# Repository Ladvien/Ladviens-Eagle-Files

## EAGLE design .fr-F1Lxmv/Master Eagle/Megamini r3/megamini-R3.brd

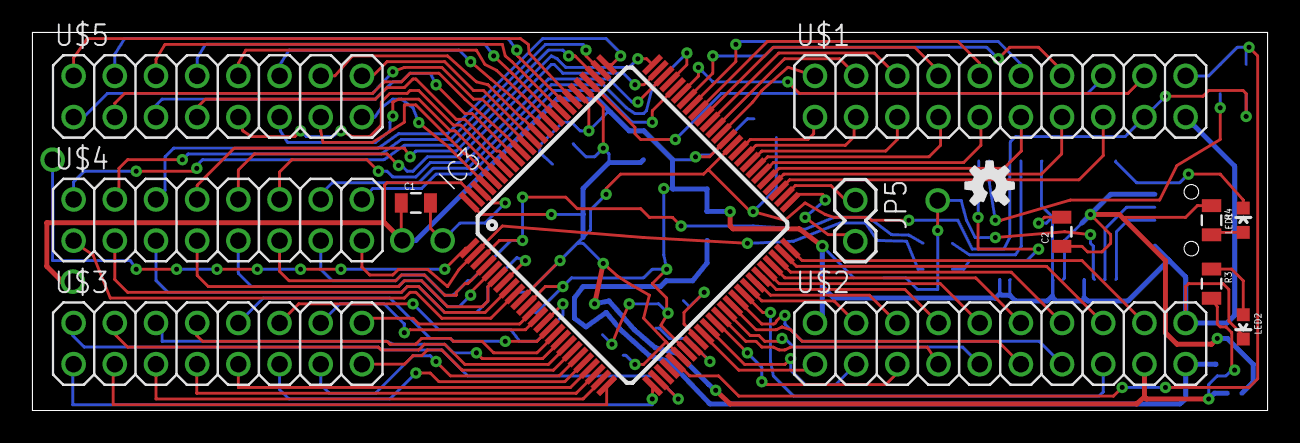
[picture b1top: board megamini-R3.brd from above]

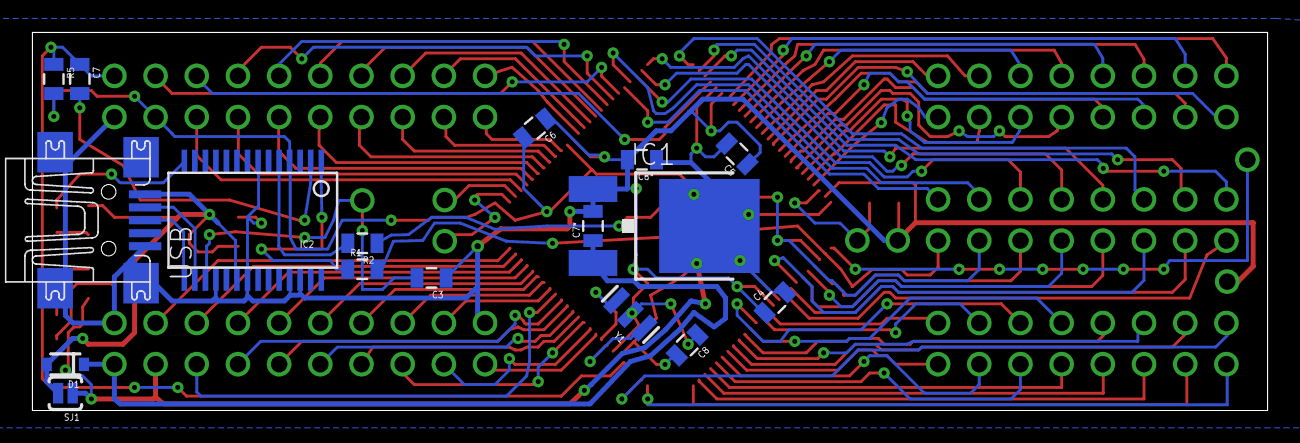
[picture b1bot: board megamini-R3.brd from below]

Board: 2 copper layers, 76.2 x 23.3 mm, 37 parts (17 on the bottom side), 101 nets.

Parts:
C1, C2, C3, C4, C5, C6, C7, C8: 100nF; 0805
C7*, C8*: 10uF; 0805
D1: SOD-323
IC1: NCP1117-5.0; DPACK
IC2: FT232RLSSOP; SSOP28DB
IC3: ATMEGA2560-16AU; TQFP100
JP1, JP2, JP3, JP4, JP6: M01SMDNS; 1X01NS
JP5: 1X02
LED1, LED2: LED-0603
R1, R2, R3, R4: 0805
R5: 10k; 0805
SJ1: SOLDERJUMPERNO; SJ_2S-NO
U$1, U$2: M10X2; 2X10
U$3, U$4, U$5: M08X2; 2X8_SMALL
U$6: OSHW-LOGOS; OSHW-LOGO-S
U$7: CREATIVE_COMMONS
USB: UX60-MB-5ST
Y1: RESONATORSMD; RESONATOR-SMD

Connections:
G0: IC3.51, JP5.2
G1: IC3.52, JP5.1
G2: IC3.70, U$1.18
GND: C1.1, C2.2, C3.1, C4.1, C5.1, C6.1, C7*.2, C8.1, C8*.2, IC1.1, IC2.7, IC2.18, IC2.21, IC2.25, IC2.26, IC3.11, IC3.32, IC3.62, IC3.81, IC3.99, JP2.1, JP3.1, LED2.C, U$1.19, U$2.2, U$2.20, USB.5, Y1.2
unnamed: IC2.16, USB.2
unnamed: IC3.1, JP1.1
unnamed: IC2.15, USB.3
unnamed: C7.2, IC2.2
unnamed: IC2.1, R1.1
unnamed: IC2.5, R2.2
unnamed: C3.2, IC2.17, JP4.1
unnamed: IC3.33, Y1.1
unnamed: IC3.34, Y1.3
unnamed: LED2.A, R3.1
unnamed: LED1.A, R4.2
unnamed: IC2.14, LED1.C
unnamed: C1.2, IC3.98, JP6.1
PA0: IC3.78, U$4.2
PA1: IC3.77, U$4.4
PA2: IC3.76, U$4.6
PA3: IC3.75, U$4.8
PA4: IC3.74, U$4.10
PA5: IC3.73, U$4.12
PA6: IC3.72, U$4.14
PA7: IC3.71, U$4.16
PB0: IC3.19, U$3.15
PB1: IC3.20, U$3.13
PB2: IC3.21, U$3.11
PB3: IC3.22, U$3.9
PB4: IC3.23, U$3.7
PB5: IC3.24, U$3.5
PB6: IC3.25, U$3.3
PB7: IC3.26, U$3.1
PC0: IC3.53, U$1.15
PC1: IC3.54, U$1.13
PC2: IC3.55, U$1.11
PC3: IC3.56, U$1.9
PC4: IC3.57, U$1.7
PC5: IC3.58, U$1.5
PC6: IC3.59, U$1.3
PC7: IC3.60, U$1.1
PD0: IC3.43, U$2.4
PD1: IC3.44, U$2.6
PD2: IC3.45, U$2.8
PD3: IC3.46, U$2.10
PD4: IC3.47, U$2.12
PD5: IC3.48, U$2.14
PD6: IC3.49, U$2.16
PD7: IC3.50, U$2.18
PE0: IC3.2, R1.2, U$4.15
PE1: IC3.3, R2.1, U$4.13
PE2: IC3.4, U$4.11
PE3: IC3.5, U$4.9
PE4: IC3.6, U$4.7
PE5: IC3.7, U$4.5
PE6: IC3.8, U$4.3
PE7: IC3.9, U$4.1
PF0: IC3.97, U$5.15
PF1: IC3.96, U$5.13
PF2: IC3.95, U$5.11
PF3: IC3.94, U$5.9
PF4: IC3.93, U$5.7
PF5: IC3.92, U$5.5
PF6: IC3.91, U$5.3
PF7: IC3.90, U$5.1
PH0: IC3.12, U$3.16
PH1: IC3.13, U$3.14
PH2: IC3.14, U$3.12
PH3: IC3.15, U$3.10
PH4: IC3.16, U$3.8
PH5: IC3.17, U$3.6
PH6: IC3.18, U$3.4
PH7: IC3.27, U$3.2
PJ0: IC3.63, U$1.2
PJ1: IC3.64, U$1.4
PJ2: IC3.65, U$1.6
PJ3: IC3.66, U$1.8
PJ4: IC3.67, U$1.10
PJ5: IC3.68, U$1.12
PJ6: IC3.69, U$1.14
PJ7: IC3.79, U$1.16
PK0: IC3.89, U$5.16
PK1: IC3.88, U$5.14
PK2: IC3.87, U$5.12
PK3: IC3.86, U$5.10
PK4: IC3.85, U$5.8
PK5: IC3.84, U$5.6
PK6: IC3.83, U$5.4
PK7: IC3.82, U$5.2
PL0: IC3.35, U$2.1
PL1: IC3.36, U$2.3
PL2: IC3.37, U$2.5
PL3: IC3.38, U$2.7
PL4: IC3.39, U$2.9
PL5: IC3.40, U$2.11
PL6: IC3.41, U$2.13
PL7: IC3.42, U$2.15
RESET: C7.1, IC3.30, R5.1, U$1.20
USB5V: C2.1, D1.2, IC2.20, R4.1, SJ1.2, USB.1
VCC: C4.2, C5.2, C6.2, C8.2, C8*.1, IC1.4, IC2.4, IC3.10, IC3.31, IC3.61, IC3.80, IC3.100, R3.2, R5.2, SJ1.1, U$1.17, U$2.17
VIN: C7*.1, D1.1, IC1.3, U$2.19

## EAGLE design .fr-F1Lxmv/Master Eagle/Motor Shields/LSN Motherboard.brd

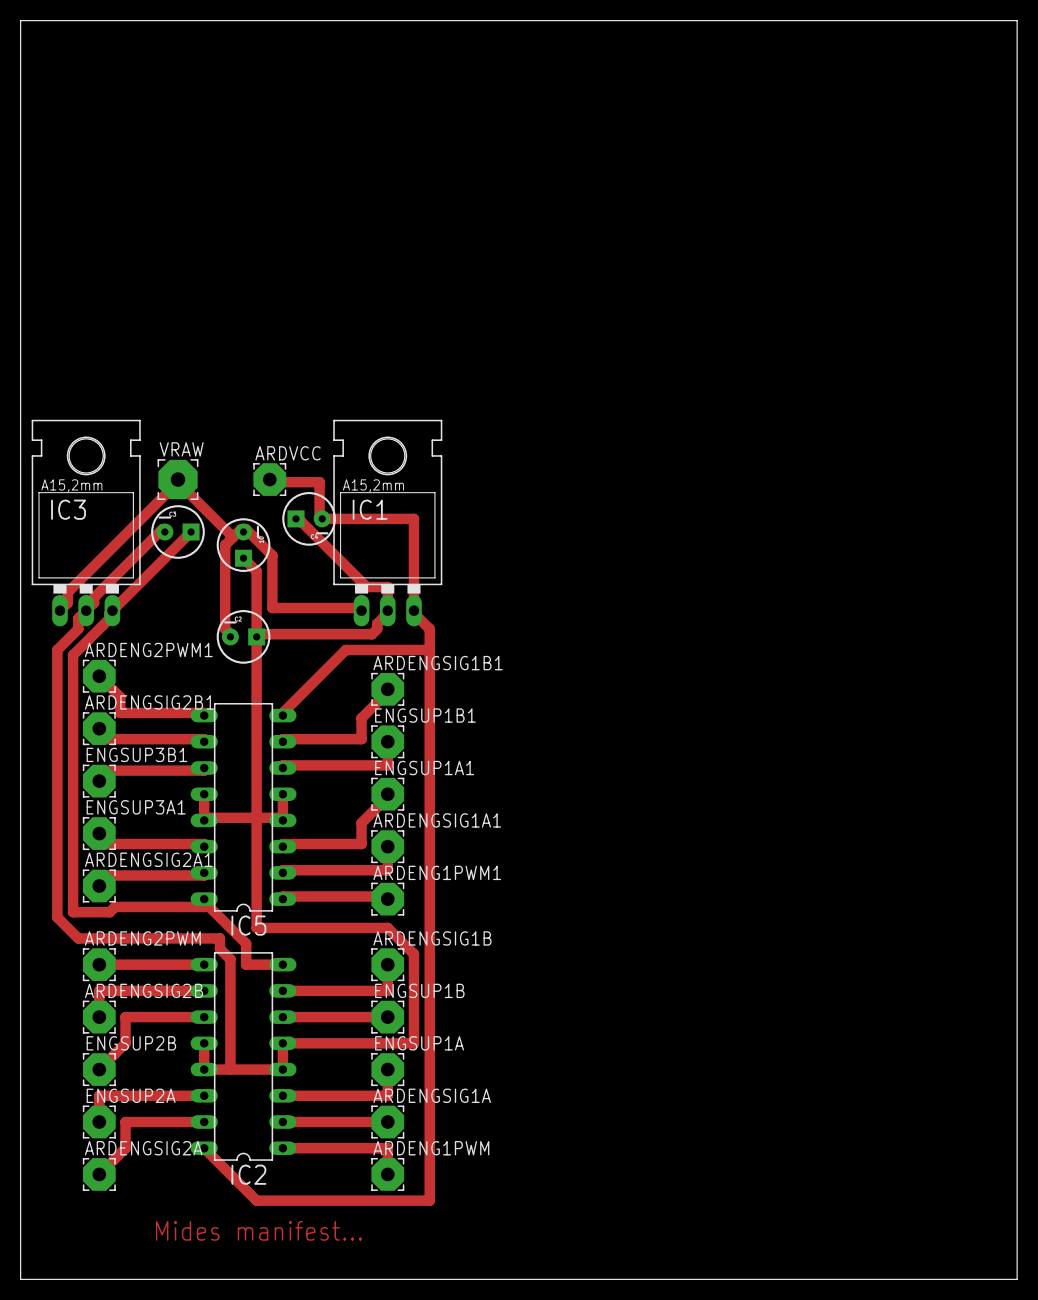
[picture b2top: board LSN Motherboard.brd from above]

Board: 2 copper layers, 96.5 x 121.9 mm, 30 parts (0 on the bottom side), 24 nets.

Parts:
10: 10; CPOL-RADIAL-10UF-25V
ARDENG1PWM, ARDENG1PWM1: Eng 1 Pwm; 3,17/1,3
ARDENG2PWM, ARDENG2PWM1: Eng2 Pwm; 3,17/1,3
ARDENGSIG1A, ARDENGSIG1A1: Eng Sig 1A; 3,17/1,3
ARDENGSIG1B, ARDENGSIG1B1: Eng Sig 1B; 3,17/1,3
ARDENGSIG2A, ARDENGSIG2A1: Eng Sig 2A; 3,17/1,3
ARDENGSIG2B, ARDENGSIG2B1: Eng Sig 2B; 3,17/1,3
ARDVCC: Ard VCC; 3,17/1,3
C2: 10; CPOL-RADIAL-10UF-25V
C3, C4: .1; CPOL-RADIAL-10UF-25V
ENGSUP1A, ENGSUP1A1: Eng Sup 1A; 3,17/1,3
ENGSUP1B, ENGSUP1B1: Eng Sup 1B; 3,17/1,3
ENGSUP2A, ENGSUP3A1: Eng Sup 2A; 3,17/1,3
ENGSUP2B, ENGSUP3B1: Eng Sup 2B; 3,17/1,3
IC1: 5v; 78XXL
IC2, IC5: SN754410; DIP16
IC3: 12v; 78XXL
VRAW: VRaw; 3,81/1,4

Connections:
ARDENGSIG1A: ARDENGSIG1A.1, IC2.2
ARDENGSIG1A1: ARDENGSIG1A1.1, IC5.2
ARDENGSIG1B: ARDENGSIG1B.1, IC2.7
ARDENGSIG1B1: ARDENGSIG1B1.1, IC5.7
ARDENGSIG2B: ARDENGSIG2B.1, IC2.10
ARDENGSIG2B1: ARDENGSIG2B1.1, IC5.10
GND: 10.1, C2.1, C3.2, C4.1, IC1.GND, IC2.4, IC2.5, IC2.12, IC2.13, IC3.GND, IC5.4, IC5.5, IC5.12, IC5.13
unnamed: 10.2, C2.2, IC1.IN, IC3.IN, VRAW.1
unnamed: ARDENG1PWM.1, IC2.1
unnamed: ARDENG2PWM.1, IC2.9
unnamed: ARDENGSIG2A.1, IC2.15
unnamed: ARDENG1PWM1.1, IC5.1
unnamed: ENGSUP1A.1, IC2.3
unnamed: ENGSUP1B.1, IC2.6
unnamed: ENGSUP2B.1, IC2.11
unnamed: ENGSUP2A.1, IC2.14
unnamed: C3.1, IC2.8, IC3.OUT, IC5.16
unnamed: ARDENG2PWM1.1, IC5.9
unnamed: ARDENGSIG2A1.1, IC5.15
unnamed: ENGSUP1A1.1, IC5.3
unnamed: ENGSUP1B1.1, IC5.6
unnamed: ENGSUP3B1.1, IC5.11
unnamed: ENGSUP3A1.1, IC5.14
unnamed: ARDVCC.1, C4.2, IC1.OUT, IC2.16, IC5.8

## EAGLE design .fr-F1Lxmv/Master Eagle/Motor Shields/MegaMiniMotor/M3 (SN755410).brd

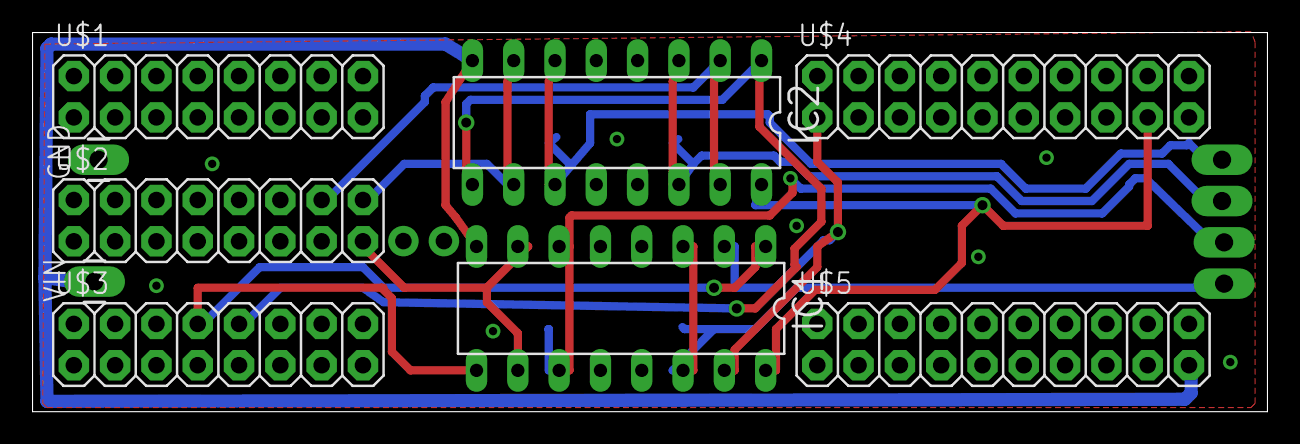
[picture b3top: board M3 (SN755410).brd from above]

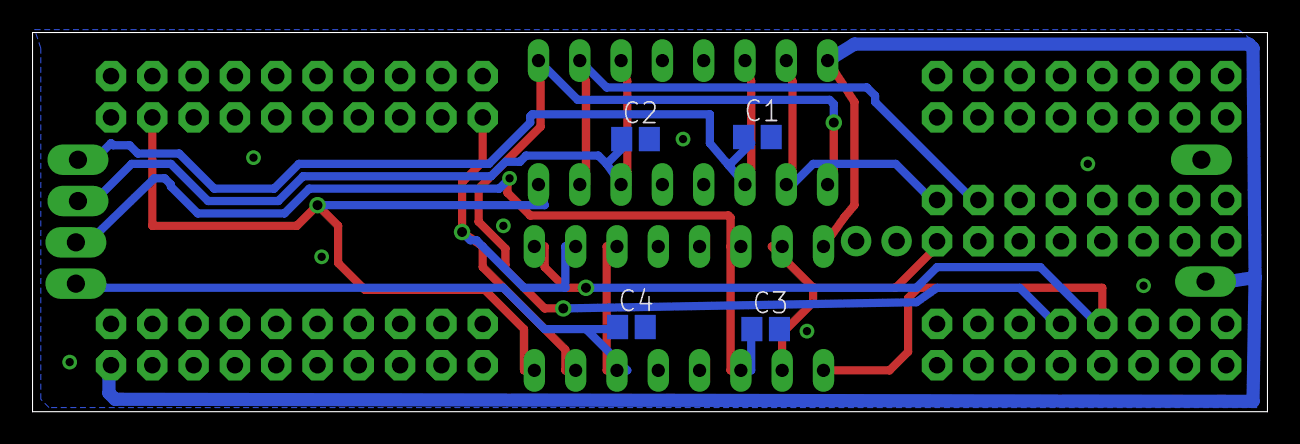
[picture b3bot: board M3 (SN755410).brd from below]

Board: 2 copper layers, 75.9 x 23.3 mm, 17 parts (4 on the bottom side), 13 nets.

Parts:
C1, C2, C3, C4: 0.1uf; C0805
GND: M01PTH_LONGPAD; 1X01_LONGPAD
IC1, IC2: SN754410; DIP16
JP1, JP2: M01SMDNS; 1X01NS
MOTA: 1X02_LONGPADS
MOTB: 1X02_LONGPADS
U$1, U$2, U$3: M08X2; 2X8
U$4, U$5: M10X2; 2X10
VIN: M01PTH_LONGPAD; 1X01_LONGPAD

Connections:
5V: IC1.16, IC2.16, U$4.17
AMA: C4.1, IC1.3, IC1.14, MOTA.2
AMB: C3.1, IC1.6, IC1.11, MOTA.1
APWM: IC1.1, IC1.9, U$3.8
ASIGA: IC1.2, IC1.15, U$4.1
ASIGB: IC1.7, IC1.10, U$2.15
BMA: C2.1, IC2.3, IC2.14, MOTB.2
BMB: C1.1, IC2.6, IC2.11, MOTB.1
BPWM: IC2.1, IC2.9, U$3.10
BSIGA: IC2.2, IC2.15, U$2.14
BSIGB: IC2.7, IC2.10, U$2.16
GND: C1.2, C2.2, C3.2, C4.2, GND.1, IC1.4, IC1.5, IC1.12, IC1.13, IC2.4, IC2.5, IC2.12, IC2.13, U$4.19
VIN: IC1.8, IC2.8, U$5.19, VIN.1

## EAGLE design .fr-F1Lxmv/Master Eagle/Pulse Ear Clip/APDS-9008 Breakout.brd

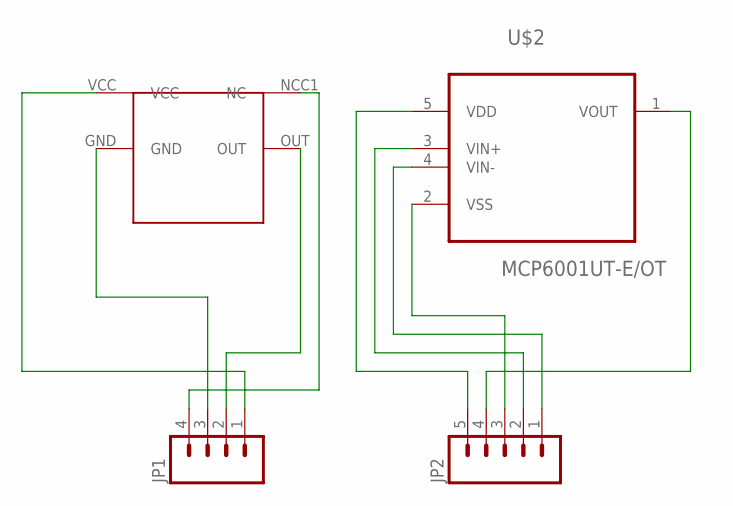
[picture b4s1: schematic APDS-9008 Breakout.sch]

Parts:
JP1: M04LOCK; 1X04_LOCK
JP2: M05LOCK; 1X05_LOCK
U$1: APDS9008
U$2: MCP6001UT-E/OT; SOT95P270X145-5N

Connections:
A-GND: JP1.3, U$1.GND
A-NC: JP1.4, U$1.NCC1 (NC)
A-OUT: JP1.2, U$1.OUT
A-VCC: JP1.1, U$1.VCC
M-VDD: JP2.5, U$2.5 (VDD)
M-VIN+: JP2.2, U$2.3 (VIN+)
M-VIN-: JP2.1, U$2.4 (VIN-)
M-VOUT: JP2.4, U$2.1 (VOUT)
M-VSS: JP2.3, U$2.2 (VSS)

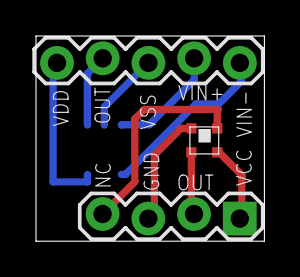
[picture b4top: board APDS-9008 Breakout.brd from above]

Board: 2 copper layers, 12.7 x 11.4 mm, 4 parts (1 on the bottom side), 9 nets.

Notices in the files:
.fr-F1Lxmv/Master Eagle/Megamini r3/megamini-R3.brd:
(C)2011 JK Devices
CC-BY-SA 3.0
parts and their libraries:
SparkFun: Released under the Creative Commons Attribution Share-Alike 3.0 License
SparkFun: http://creativecommons.org/licenses/by-sa/3.0
SparkFun: Licensing: CC v3.0 Share-Alike You are welcome to use this library for commercial purposes.
